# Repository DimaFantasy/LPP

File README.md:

# 🖨️ LPP-Laser — SDK лазерного принтера

**LPP-Laser (Linear Path Platform — Laser Edition)** — это SDK для управления и разработки встроенного программного обеспечения **лазерного принтера**, предназначенного для **печати фотошаблонов печатных плат**.  
Проект ориентирован на микроконтроллеры **STM32** (Blue Pill, Black Pill, G4).  

Добро пожаловать в проект!

**Быстрые ссылки:** [🔌 Схема подключения](#-схема-подключения-wiring-diagram) · [📜 Лицензия (GNU GPLv3)](./LICENSE)

---

## 📑 Содержание

- [Загрузка](#-загрузка)
- [Схема подключения (Wiring Diagram)](#-схема-подключения-wiring-diagram)
- [Печатные платы и схемы](#-печатные-платы-и-схемы)
- [USB-идентификаторы](#-usb-идентификаторы)
- [SDK и исходники](#-sdk-и-исходники)
- [Сообщество](#-сообщество)
- [Лицензия](#-лицензия)

---

## 📦 Загрузка

**Последняя версия управляющей программы** доступна в официальном Telegram-канале:  
👉 [https://t.me/LPP_Printer](https://t.me/LPP_Printer)

---

## 🔌 Схема подключения (Wiring Diagram)

Общая схема подключения устройства находится в корне репозитория: **[schematic.png](./schematic.png)**.

Подробное описание пинов и сигналов каждой платы — в [PCB/README.md](./PCB/README.md).

---

## 📦 Печатные платы и схемы

Все PCB-файлы проекта находятся в папке **[PCB](./PCB)** этого проекта.

| Описание | Ссылка |
|----------|--------|
| **Схема подключения (Wiring Diagram)** | [schematic.png](./schematic.png) |
| **Основная плата (MainBoard)** | Папка PCB |
| **Описание пинов и сигналов** | [PCB/README.md](./PCB/README.md) |
| **Поддерживаемые MCU** | STM32F103, STM32F401, STM32F411, STM32G431 |

**Возможности:**
- В папке **PCB** находится **основная плата (MainBoard)**, в которую можно подключить любой модуль «пилы» (Blue/Black/Green Pill).  
- Присутствует подробное **описание пинов всех плат**, включая назначение сигналов, питание и подключения периферии.  
- Даны **описания используемых чипов**, их параметры и примеры применения.  
- Вся информация позволяет создать **управляющую плату для каретки** и собрать механическую часть лазерного принтера.

---

## 🛠️ SDK и исходники

| Параметр | Значение |
|----------|----------|
| **Размер SDK** | ~152 КБ |
| **Количество файлов** | 9 файлов |
| **Изменяемые файлы** | `main.c`, `usbd_custom_hid_if.c`, `.ioc` |

### Основное приложение (App)

**Конфигурация в Keil 5:**
- **Адрес начала:** `0x08000000`  
- **Размер:** `0x7FE8` (**32 КБ**, без версии и сигнатуры)  

**Реализация:**
- Необходимо реализовать примерно **несколько функций**, включая:  
  - управление пинами,  
  - инициализацию таймера,  
  - старт/остановку DMA,  
  - передачу данных HID.  
- В исходниках приведены **подробные примеры использования функций и их документация**.

### Bootloader (Boot)

**Конфигурация в Keil 5:**
- **Адрес начала:** `0x08008000`  
- **Размер:** `0x7FE8` (**32 КБ**)  

**Реализация:**
- Необходимо реализовать только **2 функции**:  
  - обработка пакетов с HID,  
  - отправка пакетов в HID.  
- Основная задача бутлоадера — **прошить основное приложение**.  
- В исходниках приведены **подробные примеры использования функций и их документация**.

---

## 💬 Сообщество

Обсудить проект, задать вопросы или поделиться опытом можно в Telegram-группе:  
👉 [https://t.me/LPP_Printer_Chat](https://t.me/LPP_Printer_Chat)

---

## 📜 Лицензия

Проект распространяется на условиях открытой лицензии **GNU GPLv3**.  
Полный текст лицензии находится в файле **[LICENSE](./LICENSE)** в корне репозитория.

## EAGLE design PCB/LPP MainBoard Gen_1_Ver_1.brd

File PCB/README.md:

# LPP MainBoard Gen-1 (Ver. 5)

⚠️ **Статус проекта:**  
Разводка завершена, плата собрана и успешно прошла первичную проверку.  
Все найденные ошибки исправлены в текущей ревизии.  
Проект продолжает развиваться — по мере тестирования и улучшений возможны обновления.

---

## 📑 Содержание

- [Главная плата](#-главная-плата)
- [Поддерживаемые MCU](#-поддерживаемые-модули-mcu)
- [Файлы проекта](#-файлы-проекта-diptrace)
- [Распиновка Blue Pill](#распиновка-платы-blue-pill-stm32f103c8t6)
- [Таблица сигналов](#-основная-сводная-таблица-сигналов)
- [Таблица пинов](#-таблица-пинов-140)
- [Разъёмы управления (DB25)](#db25--разъёмы-управления-осями)
- [Номиналы компонентов](#номиналы-для-платы-lpp_mainboard_gen_1_ver_5)
- [Ссылки](#-ссылки-и-ресурсы)

---

## 📘 Главная плата

Первая рабочая версия основной платы LPP-Laser.  
Плата функционирует корректно; по мере дальнейшей эксплуатации и расширения функционала будет постепенно обновляться и улучшаться.

1. Все контрольные точки выведены для удобной отладки и измерений.

2. Трассировка USB выполнена по всем правилам «по феншую»:  
   дифференциальная пара согласована, импеданс выдержан, длины и симметрия соблюдены.  
   При пересечении сигнальных линий с другой стороны платы дорожки проходят **только под углом 90°**,  
   что минимизирует взаимные наводки и сохраняет целостность дифференциального сигнала.

3. Все разъёмы и не-SMD элементы припаиваются со стороны низа платы.  
   Если сверху видны соединения — это заливка (GND), паять её не нужно.

4. Минимальное расстояние между проводниками — **0.3 мм**.

5. Плату можно изготавливать **без металлизации отверстий** — достаточно пропаять только переходные отверстия вручную (соединяя верх и низ).

6. Подключение каретки — через **FFC-шлейф 24 пин, шаг 1 мм**.

---

# 🔌 Поддерживаемые модули MCU

Плата рассчитана на установку трёх типов модулей:

- **Blue Pill (STM32F103)**
- **Black Pill (STM32F401)**
- **Black Pill (STM32F411)**
- **Green Pill (STM32G431)**

---

### Важно для USB

Для **любого контроллера**, чтобы USB гарантированно работал, необходимо:

- Соединить **PA8** USB_EN с **PA12** USB_DP через резистор **1.5 кОм**.

Это позволит микроконтроллеру программно управлять подключением USB и корректно инициировать подключение к компьютеру.

---

### Особенность для Blue Pill (STM32F103)

**Если используется Blue Pill (STM32F103), потребуется паяльник:**

- Выпаять резистор **R10** с платы Blue Pill.

Это необходимо, чтобы встроенная подтяжка USB не мешала программному управлению подключением.

Все модули устанавливаются в один общий разъём,  
тип модуля выбирается с помощью пары **перемычек конфигурации**.

**Схема расположения джамперов на плате LPP MainBoard**

---

# 📂 Файлы проекта (DipTrace)

### *.dip — платы
- **LPP_MainBoard_Gen_1_Ver_5.dip** — основная плата управления.
- **LPP_Carriage_Module_Gen_1_Ver_2.dip** — рабочая версия.

### *.dch — схемы
- **LPP_MainBoard_Gen_1_Ver_5.dch**
- **LPP_Carriage_Module_Gen_1_Ver_2.dch**

---

# Распиновка платы Blue Pill (STM32F103C8T6)

Ориентация платы:
- Смотрите **сверху на плату**, надпись `STM32F103C8T6` читается прямо.
- **USB-разъём — слева**, **SWD-разъём — справа**.
- На плате два ряда по 20 контактов.
- **Нижний ряд** (ряд ближе к краю платы) нумеруется **слева направо — от USB к SWD:** пины **1–20**.
- **Верхний ряд** (ряд ближе к микроконтроллеру) нумеруется **справа налево — от SWD к USB:** пины **21–40**.
- Таким образом, нумерация повторяет **направление ножек корпуса STM32 (против часовой стрелки)**.

---

# 📊 Основная сводная таблица сигналов  
## (относительно Blue Pill STM32F103 → для STM32F411 и STM32G431)

```
№  | Сигнал        | F103 | F411 | G431 | Перенос на F411     | Перенос на F431   | Комментарий
---|---------------|------|------|------|---------------------|-------------------|-----------------------------
22 | E_STOP        | PB9  | PB9  | PB9  | Совпадает 1:1       | Совпадает 1:1     | 5 V tolerant
13 | PROBE         | PB7  | PB7  | PB7  | Совпадает 1:1       | Совпадает 1:1     | 5 V tolerant

25 | PWM_LASER     | PA0  | NRST | PA0  | На F411 = NRST      | Совпадает 1:1     |
26 | PWM_LED       | PA1  | PA0  | PA1  | Перенос PA1 → PA0   | Совпадает 1:1     |
27 | REZERV        | PA2  | PA1  | PA2  | Перекл на PWM_LASER | Совпадает 1:1     |
28 | REZERV        | PA3  | PA2  | PA3  | REZERV              | REZERV            |
29 | REZERV        | PA4  | PA3  | PA4  | REZERV              | REZERV            |

14 | X_ENC_A       | PB6  | PB6  | PB6  | Совпадает 1:1       | Совпадает 1:1     | 5 V tolerant
16 | X_ENC_B       | PB8  | PB8  | PB5  | Совпадает 1:1       | Перекл на X_ENC_B |  ⚠ На 431 BOOT0 PB8. 5 V tolerant

 4 | X_MO_ENA      | PB15 | PB15 | PB15 | Совпадает 1:1       | Совпадает 1:1     |
 2 | X_MO_R        | PB13 | PB13 | PB13 | Совпадает 1:1       | Совпадает 1:1     |
 3 | X_MO_L        | PB14 | PB14 | PB14 | Совпадает 1:1       | Совпадает 1:1     |

 1 | X_EN          | PB12 | PB12 | PB12 | Совпадает 1:1       | Совпадает 1:1      |
35 | X_STEP        | PB10 | PB1  | PB2  | Перенос PB10→PB1    | Перенос PB10→PB2   |
36 | X_DIR         | PB11 | PB2  | PB10 | Перенос PB11→PB2    | Перенос PB11→PB1   |

32 | Y_EN          | PA7  | PA6  | PA7  | Перенос PA7→PA6     | Совпадает          |
33 | Y_STEP        | PB0  | PA7  | PB0  | PB0→PA7             | Совпадает          |
34 | Y_DIR         | PB1  | PB0  | PB1  | PB1→PB0             | Совпадает          |

31 | Z_EN          | PA6  | PA5  | PA6  | Перенос PA6→PA5     | Совпадает          |
 6 | Z_STEP        | PA9  | PA9  | PA9  | Совпадает 1:1       | Совпадает 1:1      |
 7 | Z_DIR         | PA10 | PA10 | PA10 | Совпадает 1:1       | Совпадает 1:1      |

 5 | USB_EN        | PA8  | PA8  | PA8  | Совпадает 1:1       | Совпадает 1:1      |
 8 | USB_DM        | PA11 | PA11 | PA11 | Совпадает 1:1       | Совпадает 1:1      |
 9 | USB_DP        | PA12 | PA12 | PA12 | Совпадает 1:1       | Совпадает 1:1      |

18 | 5V            | 5V   | 5V   | 5V   | Совпадает 1:1       | Совпадает 1:1      |
19 | GND           | GND  | GND  | GND  | Совпадает 1:1       | Совпадает 1:1      |
```

---

# 🟩 Свободные пины

```
№   | F103 | F411 | G431 | Комментарий
----|------|------|------|-----------------
10  | PA15 | PA15 | PA15 | GPIO / JTDI
11  | PB3  | PB3  | PB3  | GPIO / SWO
12  | PB4  | PB4  | PB4  | GPIO / NJTRST
22  | PC13 | PC13 | PC13 | GPIO / Выведен как CP контрольная точка
```

---

# 🧩 Служебные и системные пины (отладка, загрузка, системные и кварцевые линии)

```
-----------------------------------------------------------------------------------------------------------------------------------------------------
Назначение              | № пина       | STM32F103          | STM32F411           | STM32G431          | Комментарий
------------------------|--------------|--------------------|---------------------|--------------------|---------------------------------------------
VBAT                    | 21           | ✅ (VBAT)          | ✅ (VBAT)          | ✅ (VBAT)          | Питание RTC / резервное питание
NRST (Reset)            | 37 / 25 / 38 | ✅ №37 = NRST      | ✅ NRST на №25,    | ✅ NRST на №38     | На разъёме: F103→37, F411→25, G431→38
BOOT0                   | —            | ✅ Есть на корпусе | ✅ Есть на корпусе | PB8                | Аппаратная линия загрузчика BOOT0 на G431
PB2 – BOOT1             | —            | ✅ Есть            | 🚫 Нет             | 🚫 Нет             | В новых сериях BOOT1 убран, используется только BOOT0
PA13 – SWDIO / JTMS     | — (корпус МК)| ✅ Есть            | ✅ Есть            | ✅ Есть            | Интерфейс SWD (данные), не трогать при отладке/прошивке
PA14 – SWCLK / JTCK     | — (корпус МК)| ✅ Есть            | ✅ Есть            | ✅ Есть            | Интерфейс SWD (такты), не трогать
PA15 – JTDI             | 10           | ✅ PA15            | ✅ PA15            | ✅ PA15            | Можно как GPIO после отключения JTAG (AFIO/SYSCFG)
PB3  – JTDO / TRACESWO  | 11           | ✅ PB3             | ✅ PB3             | ✅ PB3             | SWO/JTAG; можно как GPIO при отключении JTAG
PB4  – NJTRST           | 12           | ✅ PB4             | ✅ PB4             | ✅ PB4             | JTAG reset, при чистом SWD не нужен
PC14 – OSC32_IN (LSE)   | 23           | ✅ PC14            | ✅ PC14            | ✅ PC14            | Вход низкочастотного кварца 32.768 кГц
PC15 – OSC32_OUT (LSE)  | 24           | ✅ PC15            | ✅ PC15            | ✅ PC15            | Выход низкочастотного кварца 32.768 кГц
HSE_IN (OSC_IN)         | —            | ✅ Есть на корпусе | ✅ Есть на корпусе | ✅ Есть на корпусе | Ноги HSE не на разъёме 1–40, только у кристалла
HSE_OUT (OSC_OUT)       | —            | ✅ Есть на корпусе | ✅ Есть на корпусе | ✅ Есть на корпусе | То же, кварц 8 МГц только возле МК
3.3V                    | 20           | ✅ №20 = 3.3V      | ✅ №20 = 3.3V      | ✅ №20 = 3.3V      | Основное питание 3.3 В
3.3V (доп. вывод)       | 38 / 39      | ✅ №38 = 3.3V      | ✅ №38 = 3.3V      | ✅ №39 = 3.3V      | F103/F411: 3.3В на 38; G431: 3.3В на 39
5V                      | 18 / 40      | ✅ №18 = 5V        | ✅ №18 и №40 = 5V  | ✅ №18 = 5V        | F411 дополнительно имеет 5В на 40, у F103/G431 там GND
GND                     | 19 / 39 / 40 | ✅ 19,39,40 = GND  | ✅ 19,39 = GND     | ✅ 19,40 = GND     | F103: 3 земли; F411: GND только 19,39; G431: GND 19 и 40
-----------------------------------------------------------------------------------------------------------------------------------------------------
```

---

# 📘 Таблица пинов (1–40)  
## Blue Pill → Black Pill → STM32G431

```
№  | Blue Pill | Black Pill  | STM32G431  | F103↔F411 | F103↔G431
---|-----------|-------------|------------|-----------|-----------
1  | PB12      | PB12        | PB12       | Да        | Да
2  | PB13      | PB13        | PB13       | Да        | Да
3  | PB14      | PB14        | PB14       | Да        | Да
4  | PB15      | PB15        | PB15       | Да        | Да
5  | PA8       | PA8         | PA8        | Да        | Да
6  | PA9       | PA9         | PA9        | Да        | Да
7  | PA10      | PA10        | PA10       | Да        | Да
8  | PA11      | PA11        | PA11       | Да        | Да
9  | PA12      | PA12        | PA12       | Да        | Да
10 | PA15      | PA15        | PA15       | Да        | Да
11 | PB3       | PB3         | PB3        | Да        | Да
12 | PB4       | PB4         | PB4        | Да        | Да
13 | PB5       | PB5         | PB5        | Да        | Да
14 | PB6       | PB6         | PB6        | Да        | Да
15 | PB7       | PB7         | PB7        | Да        | Да
16 | PB8       | PB8         | PB8        | Да        | Да
17 | PB9       | PB9         | PB9        | Да        | Да
18 | 5V        | 5V          | 5V         | Да        | Да
19 | GND       | GND         | GND        | Да        | Да
20 | 3.3V      | 3.3V        | 3.3V       | Да        | Да
21 | VBAT      | VBAT        | VBAT       | Да        | Да
22 | PC13      | PC13        | PC13       | Да        | Да
23 | PC14      | PC14        | PC14       | Да        | Да
24 | PC15      | PC15        | PC15       | Да        | Да
25 | PA0       | NRST        | PA0        | Нет       | Да
26 | PA1       | PA0         | PA1        | Нет       | Да
27 | PA2       | PA1         | PA2        | Нет       | Да
28 | PA3       | PA2         | PA3        | Нет       | Да
29 | PA4       | PA3         | PA4        | Нет       | Да
30 | PA5       | PA4         | PA5        | Нет       | Да
31 | PA6       | PA5         | PA6        | Нет       | Да
32 | PA7       | PA6         | PA7        | Нет       | Да
33 | PB0       | PA7         | PB0        | Нет       | Да
34 | PB1       | PB0         | PB1        | Нет       | Да
35 | PB10      | PB1         | PB2        | Нет       | Нет
36 | PB11      | PB2         | PB10       | Нет       | Нет
37 | NRST      | PB10        | PB11       | Нет       | Нет
38 | 3.3V      | 3.3V        | NRST       | Да        | Нет
39 | GND       | GND         | 3.3V       | Да        | Нет
40 | GND       | 5V          | GND        | Нет       | Да
```

---

# DB25 — разъёмы управления осями

## DB25 (Мама, вид спереди)

```
 \ 13 12 11 10  9  8  7  6  5  4  3  2  1 /
  \ 25 24 23 22 21 20 19 18 17 16 15 14  /
   ------------------------------------
```

## DB25 (Папа, вид спереди)

```
  \ 1  2  3  4  5  6  7  8  9 10 11 12 13 /
   \ 14 15 16 17 18 19 20 21 22 23 24 25 /
    -------------------------------------
```

---

## Распиновка DB25

```
Пин | Назначение
----|-----------------
 2  | X_STEP
 3  | X_DIR
 4  | X_ENABLE

 5  | Y_STEP
 6  | Y_DIR
 7  | Y_ENABLE

 8  | Z_STEP
 9  | Z_DIR
 17  | Z_ENABLE
 
 15  | PROBE
 13  | E_STOP
```

---

# Номиналы для платы LPP_MainBoard_Gen_1_Ver_5

## Резисторы
- SMD — Резисторы, посадочные места универсальные **0805 / 1206**
- Все подтягивающие без номинала, номинал: **1…10 кОм**

## Конденсаторы
- SMD — Кондесаторы, посадочные места универсальные **0805 / 1206**
- SMD — Кондесаторы, все без номинала, номинал: **0.1 мкФ**
- Тантал низковольтный (2 шт, от 6 В): **10 мкФ и выше**
- Электролит низковольтный (2 шт, от 6 В): **100 мкФ и выше**
- Электролит высоковольтный (1 шт, от 24 В): **1000 мкФ и выше**

## USB Хаб 
- FE1.1S — смотрите даташит. Там нужен всего один резистор 2,7 кОм и пара конденсаторов для фильтрации питания. Подойдут практически любые.

## Мосты двигателя
(можно не ставить, если ось X — шаговик или BLDC)

- **BTN7933** — 18 В / 43 А  
- **IFX007T** — 38 В / 55 А  

### Совместимые аналоги (один корпус и пин-аут — TO-263-7)

**Infineon NovalithIC™ семейство (полная совместимость по корпусу и ножкам):**

- **BTS7960 / BTS7960B** — классика (устаревает)
- **BTN7930B / BTN7933B** — 18 В / ~43 А
- **BTN7960B / BTN7960TA**
- **BTN7970B / BTN7971B**
- **BTN8960TA / BTN8962TA**
- **BTN8980TA / BTN8982TA** ← **рекомендуется** (лучшая современная версия)
- **IFX007T** — 38 В / 55 А (самый мощный в линейке)

**Все перечисленные микросхемы имеют одинаковый корпус PG-TO263-7 и полностью совместимы по расположению ножек.**  
Можно ставить вместо друг друга без изменения разводки платы.

### Краткое сравнение
- **BTN7933B** — 18 В / 43 А  
- **IFX007T** — **38 В / 55 А** (мощнее по току и напряжению)

**Вывод:**  
Для большинства задач отлично подойдёт **BTN8982TA** или **IFX007T**.  
IFX007T заметно мощнее, если нужен запас по току и напряжению.

### Резистор SR (slew-rate)
Управляет скоростью переключения силовых транзисторов.

- Меньше сопротивление → быстрые фронты → больше помех  
- Больше сопротивление → мягкие фронты → меньше шумов

Рекомендовано:
- **0 Ω** — максимальная скорость, много помех  
- **5.1 kΩ** — оптимальный вариант (рекомендация Infineon)  
- **51 kΩ** — минимальные помехи, самые мягкие фронты  

## Драйвер MOSFET лазера непосредственно на каретке

- Транзистор напрямую управляется с выхода контроллера.  
  На затворе установлен токоограничивающий резистор, чтобы не нагружать выход контроллера ёмкостью затвора.

- Для большинства логических MOSFET этого достаточно и схема работает напрямую.

- Я рекомендую установить драйвер **MAX15070**  
  и запитать его непосредственно от питания лазера (**4–14 В**).  
  Всё просто.

### MAX15070

Отличный MOSFET-драйвер от Maxim:
- Питание от **4 В** до **14 В**
- До **7 А sink**, **3 А source**
- Логический вход: TTL/CMOS (~0.8 В LOW / ~2 В HIGH)
- Корпус: **SOT-23**
- Фронты: **примерно 5–10 нс** при ёмкости в нагрузке **1 нФ**
- Matched delay между входами: **500 пс**
- Защита от shoot-through встроена

---

# 🔗 Ссылки и ресурсы

LPP-Laser (Linear Path Platform — Laser Edition) — открытая платформа с открытым исходным кодом: SDK, ПО и прошивки для лазерной засветки фотошаблонов печатных плат.  
Скачать новые версии: https://t.me/LPP_Printer  
Обсудить и задать вопросы: https://t.me/LPP_Printer_Chat  
Исходники SDK и прошивки: https://github.com/DimaFantasy/LPP  
Исходники DLL Excellon Gerber → Image: https://github.com/DimaFantasy/gerb2img  
Все PCB-файлы проекта доступны в репозитории: https://github.com/DimaFantasy/LPP/tree/main/PCB

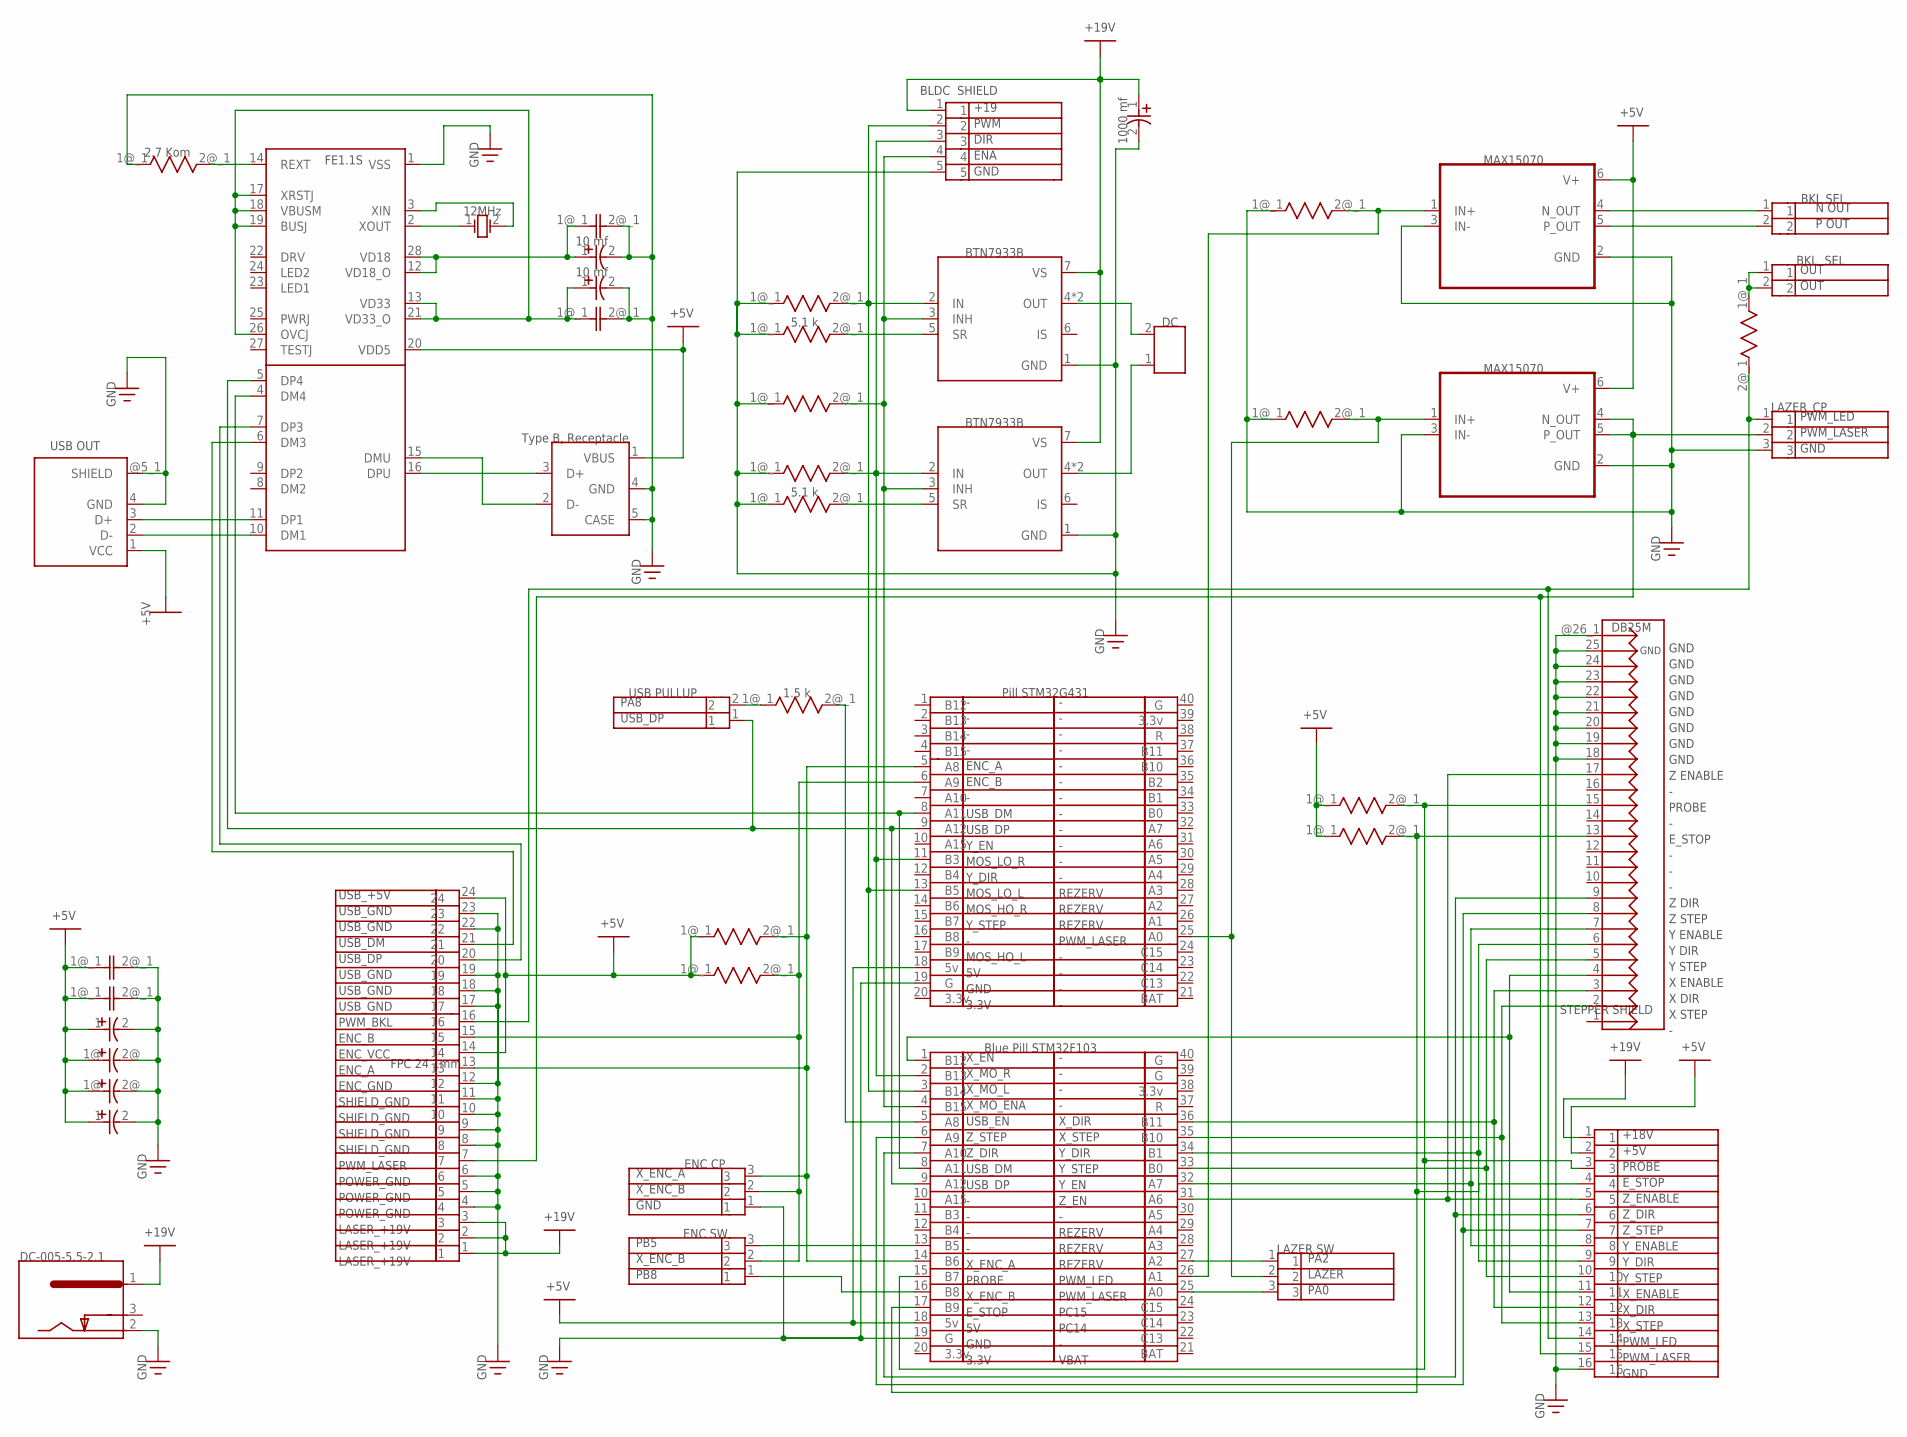
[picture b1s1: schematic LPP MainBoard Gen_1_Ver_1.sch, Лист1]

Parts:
BLDC: BLDC SHIELD; PLS_5
C1: 1000 mf; CAP_P_5MM
C2, C5, C8, C9: CAP_0805_1206; СAP_0805_1206
C3, C4: 10 mf; CAP_P_3MM
C6, C7: CAP_SMD_P_5MM; СAP_P_SMD_5MM
C10, C11: CAP_P_5MM
CNC: DB25M
DC: DC; 2_SCREW_TERM._BLK.
DC_IN: DC-005-5.5-2.1; J-1
ENC_CP: ENC CP; PLS_3
ENC_SW: ENC SW; PLS_3
FPC: FPC 24 1mm; FPC_24_1MM
IC1: FE1.1S; SOP64P600X175-28N
LAZER_CP: LAZER_CP; PLS_3
LAZER_SW: LAZER SW; PLS_3
R1: 2.7 Kom; R_0805_1206
R2, R3, R4, R6, R7, R8, R11, R12, R13, R14: R_0805_1206
R5, R9: 5.1 k; R_0805_1206
R10: 1.5 k; R_0805_1206
STEPPER_SHIELD: STEPPER SHIELD; PLS_16
U1, U4: MAX15070; SOT95P280X145-6N
U3, U5: BTN7933B; TO127P1500X440-8N
U7: Pill STM32G431; ST_PILL
U8: Blue Pill STM32F103; ST_PILL
USB_IN: Type B, Receptacle; USB-1_TYPE_B
USB_OUT: USB OUT; USB_TYPE_A_HORIZONTAL
USB_PULLUP: USB PULLUP; PLS_2
XP2, XP3: BKL SEL; PLS_2
Z: 12MHz; Q_1

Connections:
Сеть_0: BLDC.5, C1.2 (MINUS), C2.2@, C2.2@_1 (2), C3.2 (MINUS), C4.2 (MINUS), C5.2@, C5.2@_1 (2), C6.2@ (MINUS), C7.2@ (MINUS), C8.2@, C8.2@_1 (2), C9.2@, C9.2@_1 (2), C10.2 (MINUS), C11.2 (MINUS), CNC.18, CNC.19, CNC.20, CNC.21, CNC.22, CNC.23, CNC.24, CNC.25, CNC.@26, CNC.@26_1 (GND), DC_IN.2, ENC_CP.1, FPC.4, FPC.5, FPC.6, FPC.8, FPC.9, FPC.10, FPC.11, FPC.12, FPC.17, FPC.18, FPC.19, FPC.22, FPC.23, IC1.1 (VSS), LAZER_CP.3, R1.1@, R1.1@_1 (1), R2.1@, R2.1@_1 (1), R3.1@, R3.1@_1 (1), R5.1@, R5.1@_1 (1), R6.1@, R6.1@_1 (1), R7.1@, R7.1@_1 (1), R8.1@, R8.1@_1 (1), R9.1@, R9.1@_1 (1), STEPPER_SHIELD.16, U1.2 (GND), U1.3 (IN-), U3.1 (GND), U4.2 (GND), U4.3 (IN-), U5.1 (GND), U7.19 (G), U8.19 (G), USB_IN.4 (GND), USB_IN.5 (CASE), USB_OUT.4 (GND), USB_OUT.@5, USB_OUT.@5_1 (SHIELD)
Сеть_1: IC1.3 (XIN), Z.2 (OSC2)
Сеть_2: IC1.2 (XOUT), Z.1 (OSC1)
Сеть_3: DC.2, U3.4 (OUT), U3.8 (OUT)
Сеть_4: R10.2@, R10.2@_1 (2), U8.5 (A8)
Сеть_5: DC.1, U5.4 (OUT), U5.8 (OUT)
Сеть_6: ENC_CP.3, FPC.13, R13.2@, R13.2@_1 (2), U7.5 (A8), U8.14 (B6)
Сеть_7: C6.1@ (PLUS), C7.1@ (PLUS), C8.1@, C8.1@_1 (1), C9.1@, C9.1@_1 (1), C10.1 (PLUS), C11.1 (PLUS), FPC.14, FPC.24, IC1.20 (VDD5), R11.1@, R11.1@_1 (1), R12.1@, R12.1@_1 (1), R13.1@, R13.1@_1 (1), R14.1@, R14.1@_1 (1), STEPPER_SHIELD.2, U1.6 (V+), U4.6 (V+), U7.18 (5v), U8.18 (5v), USB_IN.1 (VBUS), USB_OUT.1 (VCC)
Сеть_8: IC1.11 (DP1), USB_OUT.3 (D+)
Сеть_9: R10.1@, R10.1@_1 (1), USB_PULLUP.2
Сеть_11: IC1.10 (DM1), USB_OUT.2 (D-)
Сеть_12: FPC.20, IC1.7 (DP3)
Сеть_13: CNC.3, STEPPER_SHIELD.12, U8.36 (B11)
Сеть_14: FPC.21, IC1.6 (DM3)
Сеть_15: IC1.16 (DPU), USB_IN.3 (D+)
Сеть_16: BLDC.1, C1.1 (PLUS), DC_IN.1, FPC.1, FPC.2, FPC.3, STEPPER_SHIELD.1, U3.7 (VS), U5.7 (VS)
Сеть_17: CNC.13, R12.2@, R12.2@_1 (2), STEPPER_SHIELD.4, U8.17 (B9)
Сеть_18: R9.2@, R9.2@_1 (2), U5.5 (SR)
Сеть_19: CNC.5, STEPPER_SHIELD.10, U8.33 (B0)
Сеть_20: CNC.6, STEPPER_SHIELD.9, U8.34 (B1)
Сеть_21: CNC.7, STEPPER_SHIELD.8, U8.32 (A7)
Сеть_22: CNC.8, STEPPER_SHIELD.7, U8.6 (A9)
Сеть_23: BLDC.4, R6.2@, R6.2@_1 (2), U3.3 (INH), U5.3 (INH), U8.4 (B15)
Сеть_24: IC1.15 (DMU), USB_IN.2 (D-)
Сеть_25: CNC.9, STEPPER_SHIELD.6, U8.7 (A10)
Сеть_26: CNC.17, STEPPER_SHIELD.5, U8.31 (A6)
Сеть_27: ENC_SW.1, U8.16 (B8)
Сеть_28: ENC_SW.3, U8.13 (B5)
Сеть_29: CNC.4, STEPPER_SHIELD.11, U8.1 (B12)
Сеть_30: FPC.7, LAZER_CP.2, STEPPER_SHIELD.15, U4.4 (N_OUT), U4.5 (P_OUT)
Сеть_31: R5.2@, R5.2@_1 (2), U3.5 (SR)
Сеть_32: CNC.15, R11.2@, R11.2@_1 (2), STEPPER_SHIELD.3, U8.15 (B7)
Сеть_33: ENC_CP.2, ENC_SW.2, FPC.15, R14.2@, R14.2@_1 (2), U7.6 (A9)
Сеть_34: BLDC.2, R3.2@, R3.2@_1 (2), U3.2 (IN), U7.13 (B5), U8.3 (B14)
Сеть_35: BLDC.3, R8.2@, R8.2@_1 (2), U5.2 (IN), U7.11 (B3), U8.2 (B13)
Сеть_36: CNC.2, STEPPER_SHIELD.13, U8.35 (B10)
Сеть_37: LAZER_SW.2, R7.2@, R7.2@_1 (2), U4.1 (IN+), U7.25 (A0)
Сеть_38: R2.2@, R2.2@_1 (2), U1.1 (IN+), U8.26 (A1)
Сеть_39: IC1.4 (DM4), U7.8 (A11), U8.8 (A11)
Сеть_40: IC1.5 (DP4), U7.9 (A12), U8.9 (A12), USB_PULLUP.1
Сеть_41: C4.1 (PLUS), C5.1@, C5.1@_1 (1), IC1.13 (VD33), IC1.17 (XRSTJ), IC1.18 (VBUSM), IC1.19 (BUSJ), IC1.21 (VD33_O), IC1.26 (OVCJ)
Сеть_42: C2.1@, C2.1@_1 (1), C3.1 (PLUS), IC1.12 (VD18_O), IC1.28 (VD18)
Сеть_43: IC1.14 (REXT), R1.2@, R1.2@_1 (2)
Сеть_44: LAZER_SW.3, U8.25 (A0)
Сеть_45: LAZER_SW.1, U8.27 (A2)
Сеть_46: U1.4 (N_OUT), XP2.1
Сеть_47: U1.5 (P_OUT), XP2.2
Сеть_48: R4.1@, R4.1@_1 (1), XP3.1, XP3.2
Сеть_49: FPC.16, LAZER_CP.1, R4.2@, R4.2@_1 (2), STEPPER_SHIELD.14

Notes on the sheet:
GND GND GND GND GND GND GND GND Z ENABLE - PROBE - E_STOP - - - Z DIR Z STEP Y ENABLE Y DIR Y STEP X ENABLE X DIR X STEP -
+19 PWM DIR ENA GND
USB_+5V USB_GND USB_GND USB_DM USB_DP USB_GND USB_GND USB_GND PWM_BKL ENC_B ENC_VCC ENC_A ENC_GND SHIELD_GND SHIELD_GND SHIELD_GND SHIELD_GND PWM_LASER POWER_GND POWER_GND POWER_GND LASER_+19V LASER_+19V LASER_+19V
PA2 LAZER PA0
PWM_LED PWM_LASER GND
N OUT P OUT
OUT OUT
PB5 X_ENC_B PВ8
X_EN X_MO_R X_MO_L X_MO_ENA USB_EN Z_STEP Z_DIR USB_DM USB_DP - - - - X_ENC_A PROBE X_ENC_B E_STOP 5V GND 3.3V
- - - - X_DIR X_STEP Y_DIR Y_STEP Y_EN Z_EN - REZERV REZERV REZERV PWM_LED PWM_LASER PC15 PC14 - VBAT
- - - - ENC_A ENC_B - USB_DM USB_DP Y_EN MOS_LO_R Y_DIR MOS_LO_L MOS_HO_R Y_STEP - MOS_HO_L 5V GND 3.3V
- - - - - - - - - - - - REZERV REZERV REZERV PWM_LASER - - - -
PA8 USB_DP
X_ENC_A X_ENC_B GND
+18V +5V PROBE E_STOP Z_ENABLE Z_DIR Z_STEP Y_ENABLE Y_DIR Y_STEP X_ENABLE X_DIR X_STEP PWM_LED PWM_LASER GND
BLDC SHIELD
1000 mf
10 mf
GND
DB25M
DC-005-5.5-2.1
ENC CP
ENC SW
FPC 24 1mm
FE1.1S
LAZER_CP
LAZER SW
+19V
+5V
2.7 Kom
5.1 k
1.5 k
STEPPER SHIELD
MAX15070
BTN7933B
Pill STM32G431
Blue Pill STM32F103
Type B, Receptacle
USB OUT
USB PULLUP

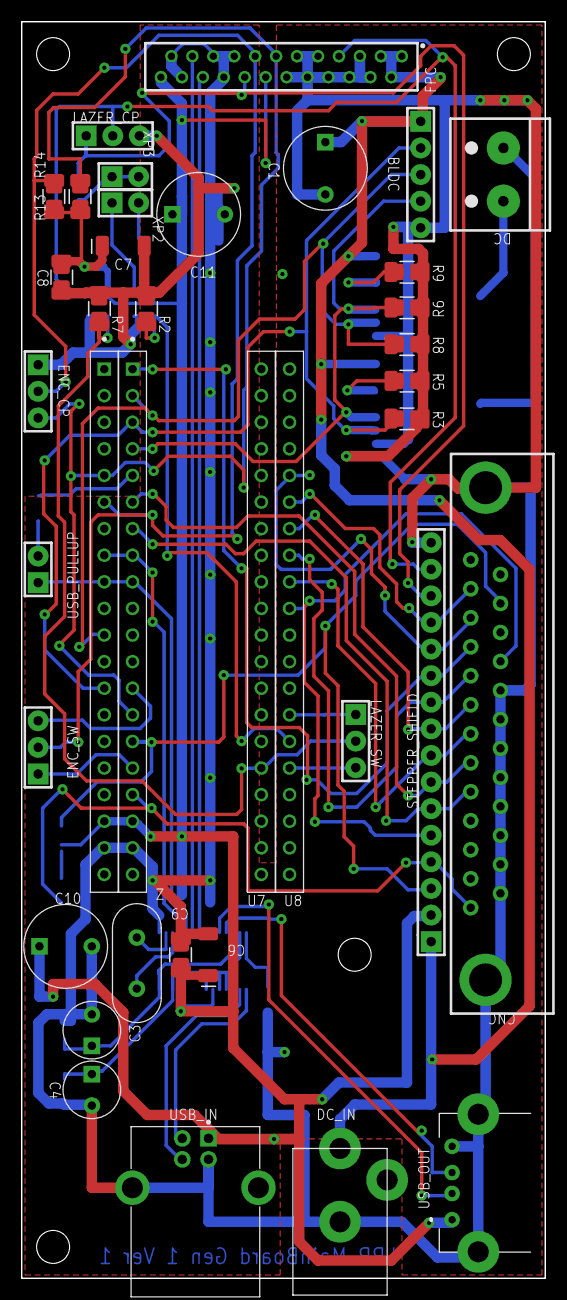
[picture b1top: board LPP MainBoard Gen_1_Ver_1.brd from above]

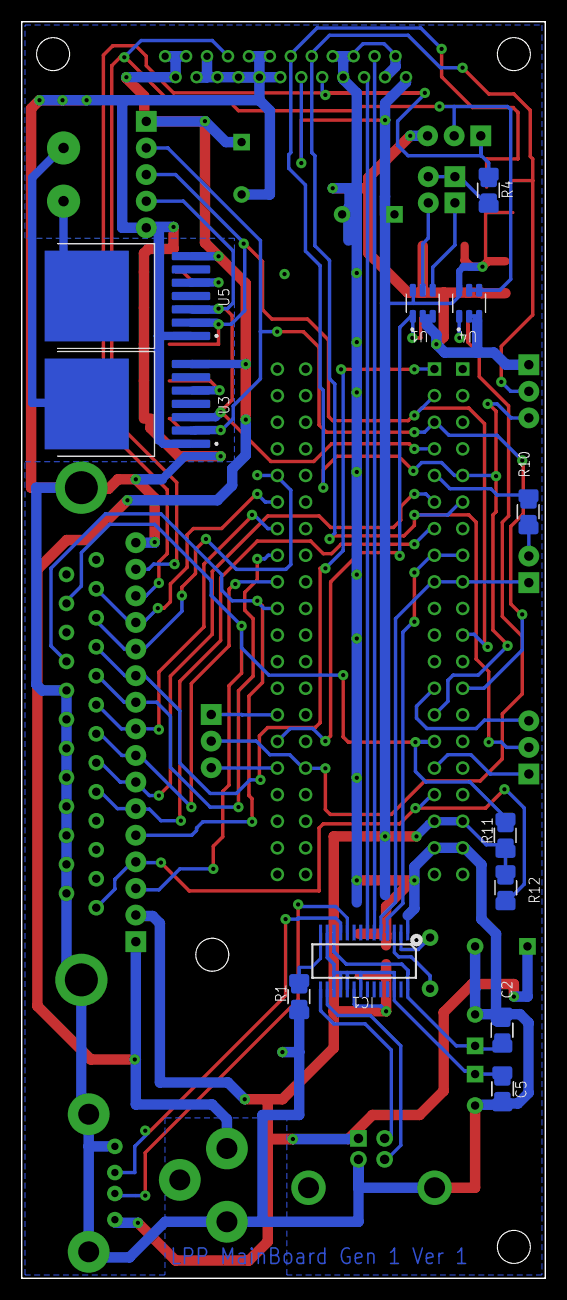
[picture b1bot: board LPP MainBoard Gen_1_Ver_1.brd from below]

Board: 2 copper layers, 50.0 x 120.0 mm, 48 parts (12 on the bottom side), 49 nets.

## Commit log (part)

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2025-11-02 new file: .gitignore new file: BOOT_STM32F103Cx/.mxproject new file: BOOT_STM32F103Cx/Boot.ioc new file: BOOT_STM32F103Cx/Core/Inc/main.h new file: BOOT_STM32F103Cx/Core/Inc/stm32f1xx_hal_conf.h new 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
2025-11-02 new file: HELP.md
2025-11-02 renamed: HELP.md -> README.md
2025-11-02 modified: README.md
2025-11-02 deleted: "LPP_STM32F103Cx/LPP_STM32F103Cx \342\200\224 \320\272\320\276\320\277\320\270\321\217.ioc" modified: LPP_STM32F103Cx/MDK-ARM/LPP_STM32F103Cx.uvguix.user modified: README.md
2025-11-02 deleted: .gitignore
2025-11-02 modified: LPP_SDK/configs/lpp_config_f103.h modified: LPP_SDK/configs/lpp_config_f411.h modified: LPP_SDK/configs/lpp_config_g431.h modified: LPP_SDK/lpp_sdk.c modified: LPP_SDK/lpp_sdk.h
2025-11-02 new file: USB_HID_DEMO/README.md
2025-11-03 new file: LPP_SDK/README.md
2025-11-03 modified: LPP_SDK/README.md
2025-11-04 modified: LPP_SDK/lpp_sdk.c modified: LPP_STM32F103Cx/MDK-ARM/JLinkLog.txt modified: LPP_STM32F103Cx/MDK-ARM/LPP_STM32F103Cx.uvguix.user modified: LPP_STM32F103Cx/MDK-ARM/LPP_STM32F103Cx.uvoptx modif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
2025-11-05 Changes to be committed: modified: LPP_SDK/lpp_sdk.c modified: LPP_STM32F103Cx/Core/Src/main.c modified: LPP_STM32F103Cx/MDK-ARM/JLinkLog.txt modified: LPP_STM32F103Cx/MDK-ARM/LPP_STM32F103Cx.uvguix.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
2025-11-05 modified: LPP_SDK/lpp_sdk.c
2025-11-05 modified: LPP_STM32F103Cx/Core/Src/main.c modified: LPP_STM32F103Cx/MDK-ARM/LPP_STM32F103Cx.uvguix.user modified: LPP_STM32F103Cx/MDK-ARM/LPP_STM32F103Cx.uvoptx modified: LPP_STM32F103Cx/MDK-ARM/LPP_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
2025-11-15 modified: LPP_STM32F103Cx/MDK-ARM/LPP_STM32F103Cx.uvguix.user renamed: LPP_STM32G431Cx/Schematic Prints.pdf -> LPP_STM32G431Cx/Schematic Prints_64.pdf new file: PCB/LPP MainBoard Gen_1_Ver_1.brd new 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
2025-11-15 modified: PCB/README.md
2025-11-15 modified: PCB/LPP_MainBoard_Gen_1_Ver_1.dip new file: PCB/LPP_MainBoard_Gen_1_Ver_1/Through.drl modified: PCB/README.md
2025-11-16 modified: PCB/LPP MainBoard Gen_1_Ver_1.brd modified: PCB/LPP MainBoard Gen_1_Ver_1.dch modified: PCB/LPP MainBoard Gen_1_Ver_1.sch modified: PCB/LPP_MainBoard_Gen_1_Ver_1.dip deleted: PCB/LPP_MainBo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
2025-11-17 modified: PCB/LPP MainBoard Gen_1_Ver_1.brd modified: PCB/LPP MainBoard Gen_1_Ver_1.dch modified: PCB/LPP MainBoard Gen_1_Ver_1.sch modified: PCB/LPP_MainBoard_Gen_1_Ver_1.dip new file: PCB/LPP_MainB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
2025-11-18 new file: PCB/LPP MainBoard Gen_1_Ver_1.kicad_dru renamed: PCB/LPP MainBoard Gen_1_Ver_1.dch -> PCB/LPP_MainBoard_Gen_1_Ver_1.dch modified: PCB/LPP_MainBoard_Gen_1_Ver_1.dip modified: PCB/LPP_MainBoa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
2025-11-18 modified: PCB/LPP MainBoard Gen_1_Ver_1.brd modified: PCB/LPP MainBoard Gen_1_Ver_1.sch
2025-11-18 modified: PCB/LPP MainBoard Gen_1_Ver_1.sch modified: PCB/LPP_MainBoard_Gen_1_Ver_1.dch modified: PCB/README.md
2025-11-20 modified: PCB/LPP MainBoard Gen_1_Ver_1.brd modified: PCB/LPP MainBoard Gen_1_Ver_1.sch modified: PCB/LPP_MainBoard_Gen_1_Ver_1.dch modified: PCB/LPP_MainBoard_Gen_1_Ver_1.dip
2025-11-21 modified: PCB/LPP_MainBoard_Gen_1_Ver_1.dch modified: PCB/LPP_MainBoard_Gen_1_Ver_1.dip new file: "PCB/LPP_MainBoard_Gen_1_Ver_1/1 - \320\222\320\265\321\200\321\205\320\275\320\270\320\271.gbr" new 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
2025-12-03 modified: LPP_STM32F103Cx/Core/Src/main.c modified: LPP_STM32F103Cx/LPP_STM32F103Cx.ioc modified: LPP_STM32F103Cx/MDK-ARM/JLinkLog.txt modified: LPP_STM32F103Cx/MDK-ARM/LPP_STM32F103Cx.uvguix.user mo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
2025-12-03 modified: PCB/LPP MainBoard Gen_1_Ver_1.brd deleted: "PCB/LPP_MainBoard_Gen_1_Ver_1 \342\200\224 \320\272\320\276\320\277\320\270\321\217.dch" deleted: "PCB/LPP_MainBoard_Gen_1_Ver_1 \342\200\224 \32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
2025-12-03 modified: PCB/LPP MainBoard Gen_1_Ver_1.brd modified: PCB/LPP_MainBoard_Gen_1_Ver_1.dip
2025-12-04 modified: LPP_STM32F103Cx/MDK-ARM/JLinkLog.txt modified: LPP_STM32F103Cx/MDK-ARM/LPP_STM32F103Cx.uvguix.user modified: PCB/LPP MainBoard Gen_1_Ver_1.brd modified: PCB/LPP_MainBoard_Gen_1_Ver_1.dip
2025-12-04 modified: LPP_SDK/lpp_sdk.c modified: LPP_SDK/lpp_sdk.h modified: LPP_STM32F103Cx/Core/Src/main.c modified: LPP_STM32F103Cx/MDK-ARM/JLinkLog.txt modified: LPP_STM32F103Cx/MDK-ARM/LPP_STM32F103Cx.uvgu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
2025-12-04 new file: PCB/LPP_MainBoard_Gen_1_Ver_1.brd renamed: PCB/LPP MainBoard Gen_1_Ver_1.sch -> PCB/LPP_MainBoard_Gen_1_Ver_1.sch
2025-12-07 modified: LPP_SDK/lpp_sdk.c modified: LPP_SDK/lpp_sdk.h modified: LPP_STM32F103Cx/Core/Src/main.c modified: LPP_STM32F103Cx/LPP_STM32F103Cx.ioc modified: LPP_STM32F103Cx/MDK-ARM/JLinkLog.txt modified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
2025-12-09 new file: LPP_SDK/configs/lpp_config_g431_alt.h modified: LPP_STM32F103Cx/MDK-ARM/LPP_STM32F103Cx/LPP_STM32F103Cx.axf modified: LPP_STM32F103Cx/MDK-ARM/LPP_STM32F103Cx/LPP_STM32F103Cx.build_log.htm m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
2025-12-11 modified: LPP_SDK/lpp_sdk.c modified: LPP_STM32F103Cx/MDK-ARM/JLinkLog.txt modified: LPP_STM32F103Cx/MDK-ARM/LPP_STM32F103Cx.uvguix.user modified: LPP_STM32F103Cx/MDK-ARM/LPP_STM32F103Cx/LPP_STM32F10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
2025-12-17 deleted: PCB/LPP_MainBoard_Gen_1_Ver_1.brd deleted: PCB/LPP_MainBoard_Gen_1_Ver_1.sch renamed: PCB/LPP_MainBoard_Gen_1_Ver_1.dch -> PCB/LPP_MainBoard_Gen_1_Ver_2.dch renamed: PCB/LPP_MainBoard_Gen_1_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
2025-12-17 modified: LPP_STM32F103Cx/Core/Src/main.c renamed: PCB/LPP_MainBoard_Gen_1_Ver_2.dch -> PCB/LPP_MainBoard_Gen_1_Ver_3.dch renamed: PCB/LPP_MainBoard_Gen_1_Ver_2.dip -> PCB/LPP_MainBoard_Gen_1_Ver_3.d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
2025-12-20 modified: BOOT_STM32F103Cx/Boot.ioc modified: LPP_SDK/lpp_sdk.c modified: LPP_SDK/lpp_sdk.h modified: LPP_STM32F103Cx/Core/Src/main.c modified: LPP_STM32F103Cx/MDK-ARM/JLinkLog.txt modified: LPP_STM3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
2025-12-20 modified: LPP_SDK/lpp_sdk.c modified: LPP_SDK/lpp_sdk.h modified: LPP_STM32F103Cx/MDK-ARM/JLinkLog.txt modified: LPP_STM32F103Cx/MDK-ARM/LPP_STM32F103Cx.uvguix.user modified: LPP_STM32F103Cx/MDK-ARM/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
2026-01-11 deleted: BOOT_STM32F103Cx/.mxproject deleted: BOOT_STM32F103Cx/Boot.ioc deleted: BOOT_STM32F103Cx/Core/Inc/main.h deleted: BOOT_STM32F103Cx/Core/Inc/stm32f1xx_hal_conf.h deleted: BOOT_STM32F103Cx/Cor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
2026-01-11 new file: LPP_STM32F103C8Tx/.mxproject new file: LPP_STM32F103C8Tx/Core/Inc/main.h new file: LPP_STM32F103C8Tx/Core/Inc/stm32f1xx_hal_conf.h new file: LPP_STM32F103C8Tx/Core/Inc/stm32f1xx_it.h new fi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
2026-01-11 new file: BOOT_STM32F103C8Tx/.mxproject new file: BOOT_STM32F103C8Tx/BOOT_STM32F103C8Tx.ioc new file: BOOT_STM32F103C8Tx/Core/Inc/main.h new file: BOOT_STM32F103C8Tx/Core/Inc/stm32f1xx_hal_conf.h new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
2026-01-11 modified: LPP_STM32F103C8Tx/MDK-ARM/LPP_STM32F103C8Tx.uvguix.user
2026-01-11 modified: LPP_STM32F103C8Tx/MDK-ARM/LPP_STM32F103C8Tx.uvguix.user modified: PCB/LPP_MainBoard_Gen_1_Ver_4.dip
2026-01-11 modified: PCB/LPP_MainBoard_Gen_1_Ver_4.dch modified: PCB/LPP_MainBoard_Gen_1_Ver_4.dip
2026-01-12 modified: BOOT_STM32G431CBTx/MDK-ARM/BOOT_STM32G431CBTx.uvguix.user modified: LPP_SDK/lpp_sdk.c modified: LPP_STM32G431CBTx/MDK-ARM/LPP_STM32G431CBTx.uvguix.user modified: README.md
2026-01-12 new file: PCB/Backup_of___PINS.cdr new file: PCB/LPP_MainBoard_Jumper_Map.png modified: PCB/README.md
2026-01-12 deleted: PCB/STM32G431CBT6_Board_PIN.png
2026-01-15 modified: LPP_SDK/lpp_sdk.c modified: LPP_STM32G431CBTx/Core/Src/main.c modified: LPP_STM32G431CBTx/MDK-ARM/JLinkLog.txt modified: LPP_STM32G431CBTx/MDK-ARM/LPP_STM32G431CBTx.uvguix.user modified: LP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
2026-01-15 deleted: PCB/Backup_of_Backup_of_Backup_of___LPP_MainBoard_Jumper_Map.cdr deleted: PCB/Backup_of_Backup_of___LPP_MainBoard_Jumper_Map.cdr deleted: PCB/Backup_of___LPP_MainBoard_Jumper_Map.cdr
2026-02-21 modified: BOOT_STM32F103C8Tx/Core/Src/main.c modified: BOOT_STM32F103C8Tx/MDK-ARM/BOOT_STM32F103C8Tx.uvguix.user modified: BOOT_STM32F103C8Tx/MDK-ARM/BOOT_STM32F103C8Tx.uvoptx modified: BOOT_STM32F10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
2026-02-27 modified: BOOT_STM32F103C8Tx/MDK-ARM/BOOT_STM32F103C8Tx/BOOT_STM32F103C8Tx.htm modified: BOOT_STM32F103C8Tx/MDK-ARM/BOOT_STM32F103C8Tx/BOOT_STM32F103C8Tx.map modified: BOOT_STM32F411CEUx/MDK-ARM/BOOT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
2026-03-05 modified: LPP_STM32F103C8Tx/Core/Src/main.c modified: LPP_STM32F103C8Tx/MDK-ARM/LPP_STM32F103C8Tx.uvguix.user modified: LPP_STM32F103C8Tx/MDK-ARM/LPP_STM32F103C8Tx/LPP_STM32F103C8Tx.axf modified: LPP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
2026-03-05 modified: PCB/README.md modified: README.md
2026-03-05 deleted: LPP_SDK/configs/lpp_config_g431_alt.h modified: PCB/README.md modified: README.md
2026-03-08 modified: PCB/LPP_MainBoard_Gen_1_Ver_5.dch modified: PCB/LPP_MainBoard_Gen_1_Ver_5.dip deleted: USB_HID_DEMO/HID2.cpp deleted: USB_HID_DEMO/README.md deleted: USB_HID_DEMO/main.c deleted: USB_HID_DE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
2026-03-11 new file: PCB/Remove_R10_on_Bluepill.png
2026-03-11 modified: PCB/LPP_MainBoard_Gen_1_Ver_5.dch modified: PCB/LPP_MainBoard_Gen_1_Ver_5.dip
2026-04-14 modified: BOOT_STM32F103C8Tx/MDK-ARM/BOOT_STM32F103C8Tx/BOOT_STM32F103C8Tx.axf modified: BOOT_STM32F103C8Tx/MDK-ARM/BOOT_STM32F103C8Tx/BOOT_STM32F103C8Tx.build_log.htm modified: BOOT_STM32F103C8Tx/MD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
2026-04-24 modified: LPP_SDK/lpp_sdk.c modified: LPP_STM32F103C8Tx/MDK-ARM/LPP_STM32F103C8Tx.uvguix.user modified: LPP_STM32F103C8Tx/MDK-ARM/LPP_STM32F103C8Tx.uvoptx modified: LPP_STM32F103C8Tx/MDK-ARM/LPP_STM3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
2026-05-21 new file: .vs/ARM_PROJECT/CopilotIndices/17.14.1641.39856/CodeChunks.db new file: .vs/ARM_PROJECT/CopilotIndices/17.14.1641.39856/SemanticSymbols.db new file: .vs/ARM_PROJECT/FileContentIndex/merges/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
2026-06-14 modified: LPP_SDK/lpp_core_gpio.c modified: LPP_SDK/lpp_sdk.c modified: LPP_SDK/lpp_sdk.h modified: LPP_STM32F103C8Tx/Core/Src/main.c new file: LPP_STM32F103C8Tx/Core/Src/main_F103.c modified: LPP_ST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
2026-06-14 deleted: .vs/ARM_PROJECT/CopilotIndices/17.14.1641.39856/CodeChunks.db deleted: .vs/ARM_PROJECT/CopilotIndices/17.14.1641.39856/SemanticSymbols.db deleted: .vs/ARM_PROJECT/FileContentIndex/merges/7d0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
2026-06-14 deleted: LPP_STM32F103C8Tx/Core/Src/main_F103.c
2026-06-21 modified: LPP_STM32F103C8Tx/Core/Src/main.c modified: LPP_STM32F103C8Tx/MDK-ARM/LPP_STM32F103C8Tx.uvguix.user modified: LPP_STM32F103C8Tx/MDK-ARM/LPP_STM32F103C8Tx/LPP_STM32F103C8Tx.axf modified: LPP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
